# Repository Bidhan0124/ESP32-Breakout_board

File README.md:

### ***ESP32 DevKit-V1 Breakout Board***

A custom breakout board for the ESP32 DevKit-V1, designed to make prototyping faster and cleaner. Instead of a jungle of  jumper wires directly onto the DevKit every project and prototype, this board gives you organized, labeled headers for every peripheral you'll  use.

This is my first PCB design project.

**What It Breaks Out:**

1. SPI x2 — Shared bus (SCK, MOSI, MISO) with independent CS lines (CS1 on D5, CS2 on D15)
2. I2C x2 — Two physical headers on the same bus (SDA on D21, SCL on D22) for connecting   multiple I2C devices simultaneously
3. UART — TX2/RX2 with VCC and GND
4. Power — Selectable between onboard 3.3V or external voltage via jumper

##### 

**Specs:**

* 3.3V operation
* Through-hole components throughout
* 2-layer board (signal on F.Cu, ground plane as well as signal on B.Cu)
* 2.54mm pitch pin headers
* Screw terminal for power input

**3D Render**

**Schematic**

**Design Decisions:**

1. Power select jumper — Instead of hardwiring 3.3V, I added a 3-pad solder jumper so the board can be powered from the onboard 3.3V rail or an external voltage source. More flexible for different prototyping scenarios where different voltages may be needed.
2. I2C pull-ups on the bus — Added 4.7kΩ pull-up resistors on SDA and SCL once on the board rather than per device. I2C is an open-drain bus so the pull-ups are a bus property, not a per-device one. Two headers on the same bus means you can connect multiple devices simultaneously as long as they are initialized with unique addresses.
3. Shared SPI bus — SPI1 and SPI2 share the same SCK, MOSI, and MISO lines but have independent CS pins. 
4. 8mm trace width for power lines and 2mm for signal lines.

**Known Limitations:**

1. D34 and D35 are input-only GPIOs on the ESP32 — they are exposed on the headers but cannot be used as outputs. 
2. No onboard decoupling capacitors — add 0.1µF caps on your board near noisy peripherals if you run into stability issues.

**Tools Used:**

KiCad 9.0

FreeRouting plugin for autorouting

**Board Status:**

&#x20;\[x] Schematic complete

&#x20;\[x] PCB layout complete

&#x20;\[x] DRC clean

&#x20;\[x] Gerbers generated

&#x20;\[ ] Fabricated

&#x20;\[ ]Tested

**Files:**

/gerbers — Fabrication files ready

ESP32\_breakout\_board.kicad\_sch — Schematic

ESP32\_breakout\_board.kicad\_pcb — PCB layout

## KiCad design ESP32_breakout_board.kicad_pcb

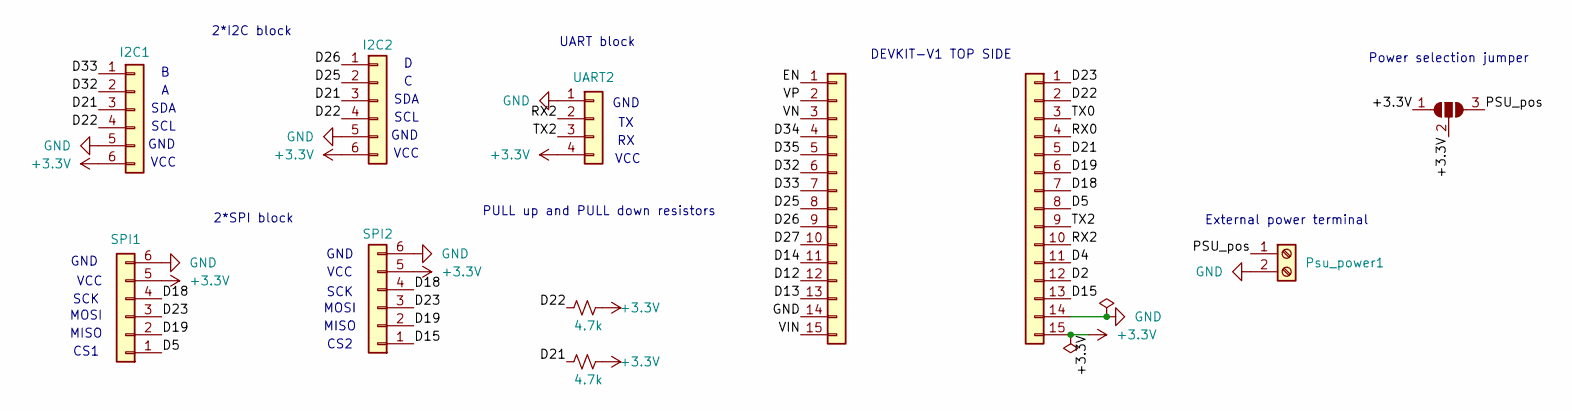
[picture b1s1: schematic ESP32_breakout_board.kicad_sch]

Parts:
I2C1, I2C2: Conn_01x06; PinHeader_1x06_P2.54mm_Vertical
J1, J2: Conn_01x15; PinHeader_1x15_P2.54mm_Vertical
JP2: SolderJumper_3_Open; SolderJumper-3_P1.3mm_Open_Pad1.0x1.5mm
Psu_power1: Screw_Terminal_01x02; TerminalBlock_MaiXu_MX126-5.0-02P_1x02_P5.00mm
R2, R4: 4.7k; R_Axial_DIN0204_L3.6mm_D1.6mm_P7.62mm_Horizontal
SPI1, SPI2: Conn_01x06; PinHeader_1x06_P2.54mm_Vertical
UART2: Conn_01x04; PinHeader_1x04_P2.54mm_Vertical

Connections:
+3.3V: I2C1.6, I2C2.6, J2.15, JP2.1 (A), JP2.2 (C), R2.2, R4.2, SPI1.5, SPI2.5, UART2.4
/D2: J2.12
/D4: J2.11
/D5: J2.8, SPI1.1
/D12: J1.12
/D13: J1.13
/D14: J1.11
/D15: J2.13, SPI2.1
/D18: J2.7, SPI1.4, SPI2.4
/D19: J2.6, SPI1.2, SPI2.2
/D21: I2C1.3, I2C2.3, J2.5, R4.1
/D22: I2C1.4, I2C2.4, J2.2, R2.1
/D23: J2.1, SPI1.3, SPI2.3
/D25: I2C2.2, J1.8
/D26: I2C2.1, J1.9
/D27: J1.10
/D32: I2C1.2, J1.6
/D33: I2C1.1, J1.7
/D34: J1.4
/D35: J1.5
/EN: J1.1
/PSU_pos: JP2.3 (B), Psu_power1.1
/RX0: J2.4
/RX2: J2.10, UART2.2
/TX0: J2.3
/TX2: J2.9, UART2.3
/VIN: J1.15
/VN: J1.3
/VP: J1.2
GND: I2C1.5, I2C2.5, J1.14, J2.14, Psu_power1.2, SPI1.6, SPI2.6, UART2.1

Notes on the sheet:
MOSI
MISO
GND
GND
UART block
VCC
External power terminal
SDA
CS2
DEVKIT-V1 TOP SIDE
SCL
Power selection jumper
CS1
SCK
PULL up and PULL down resistors
2*I2C block
2*SPI block

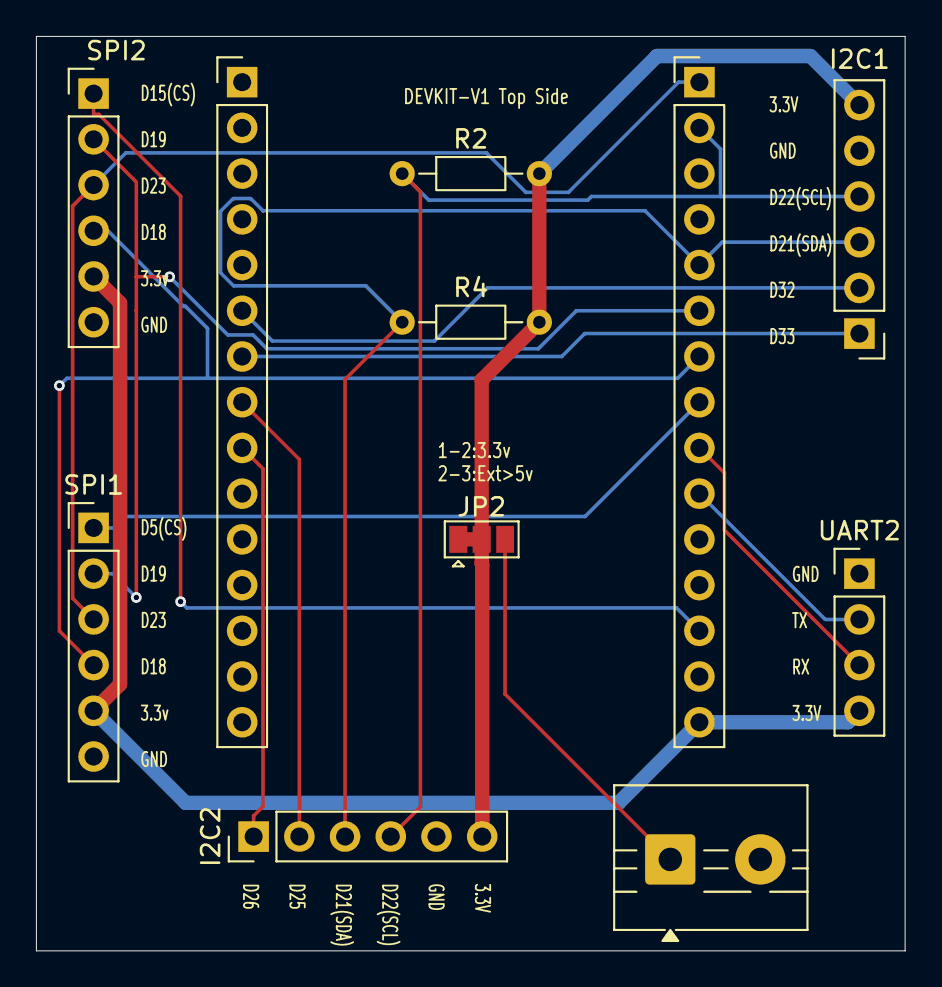
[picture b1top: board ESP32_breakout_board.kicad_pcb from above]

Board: 2 copper layers, 48.3 x 50.8 mm, 11 parts (0 on the bottom side), 16 nets.

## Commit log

2026-03-24 Breakout board design completed.
    Initial commit
2026-03-24 Update README.md
    readme updated
2026-03-24 added 3d render orthographic view png
2026-03-24 schematic added and readme changed
2026-03-24 name changes
2026-03-24 troubleshooted image not showing in readme
2026-03-24 changed design
    removed the 10k pull down after careful consideration and cleaned up the design a bit
